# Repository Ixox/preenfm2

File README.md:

# preenfm2 firmware

Ixox/preenfm2 is the official repository of the preenfm2 firmware.

You can find here the compiled firmware, its code source and some hardware files for the PCB, MCU board and cases.

To flash the preenfm2 for the first time, [follow these instructions](https://github.com/Ixox/preenfm2/tree/master/flash)

## Compiling the firmware

To compile the firmware, you'll need [arm-gcc version 4.7](https://launchpad.net/gcc-arm-embedded/+milestone/4.7-2014-q2-update)

Add the bin directory to your PATH, and run **'make'**, you'll get the list of the available targets.

```bash
$ make
You must chose a target 
Don't forget to clean between different build targets
   clean : clean build directory
   pfm : build pfm2 firmware
   pfmcv : build pfm2 firmware for Eurorack 
   installdfu : flash last compiled firmware through DFU
   zip : create zip with all inside
```
Since some refactoring, the bootloader does not compile anymore. But it's available in its binary format.

Then put your preenfm2 in [bootloader mode](http://ixox.fr/preenfm2/manual/upgrade-firmware/). Look at DFU part 4.

To flash the firmware on the preenfm2 using the DFU protocol :

```bash
make installdfu
```

Once it's done, unplug the power cable and plug it back.

## New Filters in 2.11

Many effects have been added in the firmware 2.11. They were coded by [Toltekradiation](http://ixox.fr/forum/index.php?topic=69544.0).

His github repo is [here](https://github.com/pvig/preenfm2). You'll find there some description of the different effects.

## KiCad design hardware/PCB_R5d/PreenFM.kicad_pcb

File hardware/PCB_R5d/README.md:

# Preenfm2 PCB files

Here is the preenfm2 PCB files : revision r5d.<br />
Made with [Kicad](http://kicad-pcb.org/) 3.<br />

<br />
### What's new ?<br />
Compared to r5c, there is an additional resistor that makes [the yellow oled mod](http://ixox.fr/forum/index.php?topic=69159.0) much easier.<br />

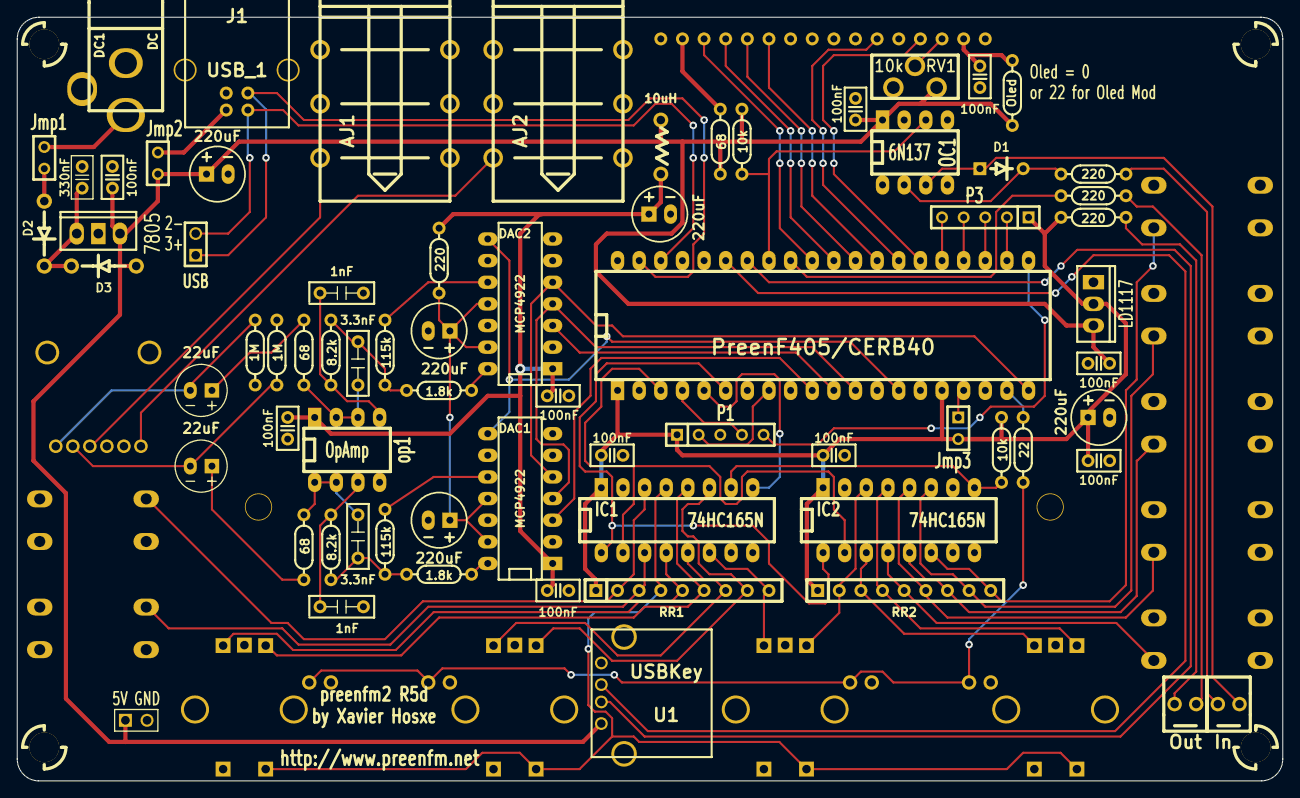
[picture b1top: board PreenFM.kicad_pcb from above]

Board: 2 copper layers, 148.6 x 89.7 mm, 92 parts (0 on the bottom side), 80 nets.

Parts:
3V1: LD1117; FMLD1117
5V1: 7805; FM7805
AJ1, AJ2: AUDIO_JACK; FMJACK
C1, C2, C3, C5, C7, C8, C10, C14, C19, C23: 100nF; FMCondeDecouplage2
C4: PreenF405/CERB40; DIP-40__600_ELL
C6, C9, C11, C13, C22: 220uF; FMCondoChimique2
C12: 330nF; FMCondeDecouplage
C15, C16: 1nF; FMCondoPlastic
C17, C18: 3.3nF; FMCondoPlastic
C20, C21: 22uF; FMCondoChimique_10uF_2
D1: 1N4148; FMDiode2
D2, D3: 1N4001; FMDiode1N4001_2
DAC1, DAC2: MCP4922; FM_mcp4922_2
DC1: DC; JACK_ALIM4
Enc1, Enc2, Enc3, Enc4: ENCODER_SW; FMEncoderWithSwitch2
IC1, IC2: 74HC165N; DIP-16__300_ELL
J1: USB_1; FMUSB2
Jmp1, Jmp2, Jmp3: Jmp; SIL-2
K2: USB; SIL-2
L1: 10uH; FMInductance
L2, L3, L4, L5: LED; FMLed
LCD1: Disp_20x4; FMLCD4x20_2
M1: In; FMMidi2
M2: Out; FMMidi2
OC1: 6N137; DIP-8__300_ELL
P1, P3: CONN_5; SIL-5
P4, P5, P6, P7: CONN_1; FMHole3mm
POW1: 5V; PIN_ARRAY_2X1
R1, R2, R3, R6: 220; FMResistance
R4, R5: 10k; FMResistance
R7, R9: 1.8k; FMResistance
R8, R10: 115k; FMResistance
R11, R14, R15: 68; FMResistance
R12, R13: 8.2k; FMResistance
R16, R17: 1M; FMResistance
R18: 22; FMResistance
R19: Oled; FMResistance
RR1, RR2: RR10k; FMRR9
RV1: 10k; FMRV2
S1, S2, S3, S4, S5, S6, S7: SWITCH; FMButton2
U1: USBKey; FMUSB_A
V1: VOLUME; FMDualPotALPS
op1: OpAmp; DIP-8__300_ELL

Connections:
+3.3V: 3V1.2, C1.1, C2.1, C4.1, C4.16, C9.1, C23.1, IC1.16, IC2.16, Jmp3.2, P1.1, P3.1, R1.2, R4.1, RR1.1, RR2.1
+5V: C6.1, C7.1, C8.1, C19.1, DAC1.1, DAC2.1, L1.2, R6.1, op1.8
+5VA: 3V1.3, 5V1.2, C3.1, C5.1, C10.1, C22.1, D3.1, Jmp2.1, L1.1, OC1.8, POW1.1, R5.2, R11.2, R19.2, RV1.3, U1.1
/AIN1: C4.22, P3.2
/AIN2: C4.23, P3.3
/AIN3: C4.24, P3.4
/AIN4: C4.25, P3.5
/DB4: C4.28, LCD1.11
/DB5: C4.29, LCD1.12
/DB6: C4.30, LCD1.13
/DB7: C4.31, LCD1.14
/E: C4.27, LCD1.6
/LED: C4.19, R18.1
/LODR: C4.17, Jmp3.1
/MCLK: C4.3, IC1.2, IC2.2
/MLD: C4.6, IC1.1, IC2.1
/MQH: C4.5, IC1.9
/RESET: C4.21, P1.5
/RR1_1: IC1.14, RR1.2, S2.2
/RR1_2: IC1.3, RR1.3, S1.2
/RR1_3: Enc1.3, Enc2.3, Enc3.3, Enc4.3, IC1.13, RR1.4
/RR1_4: Enc4.2, IC1.4, RR1.5
/RR1_5: Enc4.0, IC1.12, RR1.6
/RR1_6: Enc3.2, IC1.5, RR1.7
/RR1_7: Enc3.0, IC1.11, RR1.8
/RR1_8: Enc2.2, IC1.6, RR1.9
/RR2_1: Enc2.0, IC2.14, RR2.2
/RR2_2: Enc1.2, IC2.3, RR2.3
/RR2_3: Enc1.0, IC2.13, RR2.4
/RR2_4: IC2.4, RR2.5, S3.2
/RR2_5: IC2.12, RR2.6, S4.2
/RR2_6: IC2.5, RR2.7, S5.2
/RR2_7: IC2.11, RR2.8, S6.2
/RR2_8: IC2.6, RR2.9, S7.2
/RS: C4.26, LCD1.4
/RX: C4.33, OC1.6, R5.1
/SPI_CK: C4.12, DAC1.4, DAC2.4
/SPI_DAC1: C4.10, DAC1.3
/SPI_DAC2: C4.11, DAC2.3
/SPI_LDAC: C4.14, DAC1.8, DAC2.8
/SPI_MO: C4.20, DAC1.5, DAC2.5
/SWD_CLK: C4.8, P1.2
/SWD_IO: C4.4, P1.4
/TX: C4.32, R3.2
/USB_D+: C4.39, J1.3, K2.1
/USB_D-: C4.38, J1.2, K2.2
/USB_DN: C4.34, U1.2
/USB_DP: C4.35, U1.3
GND: 3V1.1, 5V1.1, AJ1.0, AJ2.0, C1.2, C2.2, C3.2, C4.2, C5.2, C6.2, C7.2, C8.2, C9.2, C10.2, C11.2, C12.2, C13.2, C14.2, C15.2, C16.2, C19.2, C22.2, C23.2, DAC1.12, DAC2.12, DC1.1, Enc1.1, Enc1.4, Enc2.1, Enc2.4, Enc3.1, Enc3.4, Enc4.1, Enc4.4, IC1.8, IC1.15, IC2.8, IC2.15, J1.4, L2.2, L3.2, L4.2, L5.2, LCD1.1, LCD1.5, LCD1.7, LCD1.8, LCD1.9, LCD1.10, LCD1.16, OC1.5, P1.3, POW1.2, R16.2, R17.2, RV1.1, S1.1, S2.1, S3.1, S4.1, S5.1, S6.1, S7.1, U1.4, V1.1, V1.4, op1.4
unnamed: IC1.10, IC2.9, R4.2
unnamed: AJ1.1, V1.5
unnamed: M2.1, R1.1
unnamed: C17.1, R14.1, op1.1, op1.2
unnamed: C18.1, R15.1, op1.6, op1.7
unnamed: C20.1, R14.2
unnamed: C21.1, R15.2
unnamed: DAC1.14, R7.1
unnamed: C15.1, R13.2, op1.5
unnamed: DAC2.14, R9.1
unnamed: DAC2.10, R10.1
unnamed: DAC1.10, R8.1
unnamed: C17.2, R7.2, R8.2, R12.1
unnamed: AJ2.1, V1.2
unnamed: C20.2, R16.1, V1.6
unnamed: D2.1, Jmp1.2
unnamed: DC1.3, Jmp1.1
unnamed: LCD1.15, R11.1
unnamed: C16.1, R12.2, op1.3
unnamed: J1.1, Jmp2.2
unnamed: LCD1.3, RV1.2
unnamed: M1.1, R2.1
unnamed: M2.2, R3.1
unnamed: D1.2, OC1.2, R2.2
unnamed: D1.1, M1.2, OC1.3
unnamed: C18.2, R9.2, R10.2, R13.1
unnamed: 5V1.3, C12.1, D2.2, D3.2
unnamed: C21.2, R17.1, V1.3
unnamed: C14.1, LCD1.2, R19.1
unnamed: C11.1, C13.1, DAC1.11, DAC1.13, DAC2.11, DAC2.13, R6.2
unnamed: L2.1, L3.1, L4.1, L5.1, R18.2

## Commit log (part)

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2014-01-16 Fixed velocity in ALGO17 & 18
2014-01-18 First FX commit : LP, HP, Bass, Mono.
2014-01-18 FX default value cannot be (0,0,0,0)
2014-01-26 1.B2 : fix + new mixer + CC as source + OLED screen saver + New LFO
2014-02-01 Better navigation with double press in Matrix menu
2014-02-04 1.B4 Better DX7 import
2014-02-06 New hardfault page
2014-02-06 Fixed voice allocation bugs. getFreeVoice + Timbre::preenNewNote.
2014-03-05 1.B6 : fixed glide display bug + USB aftertouch Iternal refactoring
2014-03-11 Add direction 'played' to arpeggiator
2014-03-12 1.B7 : Fixed channe 3&4 but
2014-03-13 1.B8 : arpeggiator as played + note on alocation reworked
2014-03-15 Silence warnings...
2014-03-15 Less verbose makefile
2014-03-16 Bootloader 1.11
2014-03-16 Better push timer for bootloader
2014-03-20 1.B9... Makefile & TODO updated
2014-03-20 ALGO28 : only show IM1
2014-03-22 1.B9: Bank, BankLSB and program change implemented.
2014-03-23 Removed ugly Display debug
2014-03-23 Correct version : 1.B10
2014-03-26 1.B11 : LFO.Ksyn => 16.0s + several small fixes in the LF area
2014-03-28 Experimental user-defined pattern for arpeggiator
2014-03-28 Rename engineApr to engineArp (probably just a typo)
2014-03-28 Store user arp pattern (contents might still change though)
2014-03-29 Store arpeggiator patterns in a uint32_t instead of 4 floats, allowing for 4 per timbre. Add specific editing code (rough implementation)
2014-04-02 Performance patch: mostly from Patrick perf Dowling branch.
2014-04-03 Makefile 1.B12 + KSyn display fixe bug (4.00 correctly displayed)
2014-04-09 Ensure valid menu row when switching instruments, return to last state
2014-04-10 Fix boundary case of navigation, move #define to header
2014-04-10 Change compile-time edit option a run-time configurable setting; rename to 'unlinked' editing so false default works
2014-04-11 Fix typo in matrix target (Mix3/pan3)
2014-04-12 Fix regression in navigation and use correct button for env rows
2014-04-12 Add comment
2014-04-27 Add cyclic modes for arpeggiator
2014-04-29 Minor cleanup, rename arp modes
2014-05-02 Remove unused virtual function calls, save some cycles...
2014-05-02 Remove useless code + move code to cpp
2014-05-03 Patrick bug fix
2014-05-07 Midi CC fix
2014-05-16 Firmware 1.00 ready ?
2014-06-05 Fix combo problem + firmware 1.01
2014-06-17 StepSequers & preset name flushed with presets
2014-06-29 Better name refresh
2014-07-15 Swap to page shortcuts
2014-07-15 1.03 : nrpn preset flush are now done correctly on the right midi channel
2014-08-10 Small insignifiant details
2014-09-08 Randomizer + boot sound
2014-09-08 BP middle freq is targetable from the Matrix
2014-10-12 Fix LFO with ksyn = 0.01
2015-08-09 1.07b1 Scala
2015-08-11 compilation error on Linux fixed.
2015-08-11 Lfo phases + Midi note scaling
2015-08-17 Real polyphony
2015-08-18 Fix Modwheel, Pitchbend bug
2015-08-19 1.99c : 2 midi note scales + Gate back
2015-08-20 1.99c : matrix target list updated
2015-08-27 1.99d save
2015-08-28 2.00b1 see TODO.txt
2015-08-28 2.00b1 last minute change :(
2015-10-05 First version of user waveforms
2015-10-10 All waveforms between -1.0 and 1.0
2015-10-15 2.02 : user waveform preprocessing
2016-05-08 2.03 : more CC
2016-08-24 2.05B3
2016-09-14 Breath CC to matrix source
2016-09-14 FIX : IM* target matrix can correctly decrease velocity IM
2016-09-19 Strict NRPN option added : use 7bits (CC6 only) when sufficient
2016-09-24 PreenF405 README
2016-10-11 Revert "Strict NRPN option added : use 7bits (CC6 only) when sufficient"
    This reverts commit 4ffa40c3e819c186cf1b49844e744488c2d04e78.
2016-10-12 New midi CC for arpegiator
2016-10-12 Fix missing note... Stupid return instead of continue :/
2016-10-12 2.06
2016-11-16 New svg case files
2016-11-17 hardwae/case : hardware list added
2016-11-17 Create gh-pages branch via GitHub
2016-12-16 Fix MTX* problem
2017-05-29 PCB r5d files added
2017-05-29 Better README.md
2017-07-12 Add preenF405 detailed BOM
2017-10-15 Copy feature
2017-10-16 Lokki's feature : global midi channel + hertz osc detune
2017-10-22 2.08b2 lfo rate up to 99.9hz +fixes
2017-10-23 2.08b3 : add CC for env modulators and carriers
2017-10-23 release/fw_2.08b3 firmware
2017-10-24 Matrix destination can control Carrier vs Modulatir Env*
2017-10-24 Firmware 2.08b4
2017-11-05 Fix NRPN step sequencer
2017-11-05 2.08 binary added
2017-11-05 2.08 REAMDE.md
2017-11-05 2.08 README.md changes
2017-11-07 CC cannot make filter Freq and Res > 1.00
2018-04-02 2.08b env bug fix
2018-10-13 Scala Enabled and Scale controlable through midi CC
2018-10-13 Fix Op 1&4 default combo release time
2018-10-13 2.08c was already used
2018-10-14 Reset internal cached values between notes
2018-10-27 Prevent reading null pointer when receiving midi value > max
2018-10-27 Move ARP CC to 100+ to prevent confustion with NRPN
2018-10-27 Update correctly * (preset modified) for instruments not on screen
2018-10-27 Display refresh optimisation on midi update + fix some preset display that show up when it should not
2018-12-31 Update to latest 4.7 gcc release.
2019-03-08 Van Daal Electronics CB converter PCB added
2019-03-08 Update URL
2019-04-03 Welcome Emilie in the preenfm2 code
2019-05-04 Schematics in pdf
2019-05-30 New combo bank now shows up correctly
2019-05-30 New midi channel for current instrument + new CC(119) to modify current instrument
2019-05-30 New case svg files added
2019-05-30 Analog in of P3 enabled
2019-05-30 Fix bug with Gate On when switch on
2019-05-30 Eurorack + gate + v/oct + tunable
2019-05-30 Fix Makefile
2019-05-30 Put back modifiable CV gate
2019-05-30 CVGate can trigger several instruments
2019-08-08 new filter flavour + tilt filter
2019-08-08 added lost commit
2019-08-09 tilt fix
2019-08-10 some filter tweak+code cleaning
2019-08-10 added allpass, saturator & sigmoid filters
2019-08-11 sigmoid tweak
2019-08-11 more usable range for saturator
2019-08-11 allpass filter used for a stereo enhancer filter
2019-08-13 dist & sigmoid tweak
2019-08-14 added xor & foldback distortion
2019-08-15 fixed sigmoid level + changed fold algo
2019-08-15 missing matrix filter controls added
2019-08-15 lowered resonance in tilt filter
2019-08-16 lp2 & hp2 reso saturation fix
2019-08-17 various optimizations & waveshaping here and here
2019-08-17 wrap filter added
2019-08-18 added swap~ fx + threshol voicenum attenuation
2019-08-18 fx threshold tweak
2019-08-21 hp2 bug fix + texture fx try + some tweak
2019-08-22 changed fx swap and texture to texture1 & 2 = bitmangling fx
2019-08-22 allow texture1&2 to be matrix controlled
2019-08-25 added lphp filter
2019-08-26 added BP3 + sorted fx list by use (more or less)
2019-08-26 edited readme + LPws
2019-08-26 readme update
2019-08-27 added notch & lp3 filters
2019-08-28 added PEAK, HP3, BP3 + renamed old BP3 -> BPds
2019-08-29 added bell filter
2019-08-29 various tweak + readme update
2019-08-30 wrap & fold rework + code cleaning
2019-08-30 added tone to distortion fx + tweak
2019-08-30 optimisation
2019-08-31 lp2&hp2 offset
2019-08-31 svf volume compensation
2019-09-01 code cleaning
2019-09-01 lphp & BPds resonance tweak
2019-09-02 added lowshelf & highshelf filters
2019-09-04 drastic optimizations
2019-09-05 float cast optimization
2019-09-06 sat33, sigmoid, lp resonance tweak
2019-09-10 sig, fold, wrap filter change
2019-09-11 sigm, fold, wrap
2019-09-13 FILTER_LPXOR rework
2019-09-21 svf filters cleanup, added LPSin, HPSin, BPSin
2019-09-25 lpsin now use svf lp
2019-09-27 satSin fix + optimization
2019-09-29 added doublenotch + optimization
2019-10-04 reworked pann, ap3
2019-10-05 resonant 3xap, tilt ap, sat ap, 3xnoth ap3 pan
2019-10-05 texture1&2 : added ap diffusion
2019-10-06 textures slight mod + rollback some ap filters
2019-10-10 AP4D : Diffusion allpass filter + ap fx tweak
2019-10-12 ap on svf + various tweak
2019-10-18 allpass allpass
2019-10-23 formantic filter + ap polish
2019-10-26 formant filter wip
2019-10-27 formant + ap4 fine tune
2019-11-01 tanh optimization, formant filter tweak
2019-11-05 added ladder filter
2019-11-19 wip oryx2, ladders..
2019-11-21 oryx + ladders wip
2019-11-24 formant wip
2019-11-25 formants fine tune
2019-11-30 added h3o+ filter
2019-12-01 h3o+ wip
2019-12-05 various tweak
2019-12-07 srr + tb wip
2019-12-08 tb2 + crush2 wip
2019-12-09 code cleaning + tbcrunchtweak
2019-12-10 crush wip
2019-12-11 reworked srrx2 & Svh3
2019-12-12 Alkx fine tuning
2019-12-14 Put back original README + filters part added
2019-12-14 Fix possible problem when number of voice is increased
2019-12-14 fix to allow adcIn merge
2019-12-14 velocity fix + code cleaning
2019-12-14 h3o+ : remove accent circuit
2019-12-14 accent is back on teebee filter
2019-12-15 bpds self oscillation fix
2019-12-15 18db resonance tweak
2019-12-15 peak reso curve tweak
2020-01-09 added 8 matrix sources
2020-01-09 matrixSourcePosition for CVIN fix
2020-01-11 README : makefile target list updated
2020-01-11 Add bootloader bin in zip file
2020-01-14 renamed source + oryx rollbck
2020-01-17 why not [more matrix sources] ?
2020-01-20 oryx3 rework + sources
2020-01-26 texture2 rework &+
2020-02-04 textures wip + sin f control
2020-02-05 fine tune levels
2020-02-08 filter controls wip
2020-02-09 lp3, rot
2020-02-19 + glide gate
2020-02-21 rot fix
2020-02-28 glide wip
2020-03-08 better glide
2020-03-16 articulation121
2020-03-20 glide skew...
2020-03-25 hold pb fix
2020-03-26 code cleanup
2020-03-27 end existing gliding in all cases
2020-03-28 stop voice assignation bouncing
2020-03-29 +2 more glide vals
2020-04-04 glide mods fix &+
2020-04-05 2.11 : new instrunet selection for Eurorack version
2020-04-06 mono glide over poly + cleaning
2020-04-06 polyglide branch
2020-04-15 added editor xml definitions
2020-04-30 modulator env loop
2020-05-01 added sustain in env loop
2020-05-07 bug fix & optimisation
2020-05-08 matrix seq start bug fix
2020-05-21 Destination 2 added
2020-05-21 Features from Patrice Vigouroux
2020-05-22 Dedicated #define for CPU_USAGE
2020-05-22 Fix typ
2020-05-22 Fix Dest2 lfoused for MX1/MX4
2020-05-22 Beta1 ready
2020-05-24 updates from 2.12
2020-05-27 more consistent step start result
2020-05-27 updated version
2020-05-29 stepseq fix for ENV_ATTACK destinations
2020-06-28 Not working yet
2020-06-28 Compiles
2020-07-03 CC10 & CC7 & 3 bug fixes
2020-07-03 Remove BOOTLOADER define
2020-07-04 IRQ/DMA ready to test
2020-07-04 2.12 bug fix
2020-07-05 removed GLIDE_ for lighter cpu charge
2020-07-07 Next step
2020-07-09 CS4344 fix IRQ and Frequencies
2020-07-11 matrix dest label fix
2020-07-12 Bootloader read UsbKey and DFU OK
2020-07-14 USB optimization
2020-07-22 Optimization GPIO / LCD / USART
2020-08-15 CS4344 fixes
2020-08-16 Samples are uint32 / CS4344 real 24 bits / Wait with message if no USB Key
2020-08-18 Flash README
2020-08-21 Message when no Usb Key instead of freezing
2020-08-21 CC10 & CC7 / 3 bug fixed / 192Mhz is the new default
2020-08-21 Mix4/Pan4 destination fixed / small optimization
2020-08-21 CS4344
2020-09-19 Better midi and screen boot
2020-09-20 bootlader 1.12 OK
2020-10-03 stutil debug json files
2020-10-16 Upgrade to FatFs 0.14
2020-10-25 Leave more time to USB stick to init before displaying message
2020-10-25 Fix first bit problem with i2s (sound saturation)
2020-10-25 Bootloader 1.13 (not finished)
2020-10-25 Fix screensaver
2020-10-27 Bootloader modificaiton (USB access still does not work)
2020-10-28 Bootloader 1.13 with USB access working
2020-11-06 flash/README updated
2020-11-06 flash README.md updated
2020-11-06 3D printed case added
2020-11-06 update case3DPrint/README
2021-02-15 Unisons seems to work
2021-02-16 Bug fix : load preset freeze + button shortcut
2021-02-16 Fix bug : UI + presets
2021-02-21 Unisons : CV fixed + different starting phase per voice
2021-02-22 Correct initialization of unison phases
2021-02-22 Better unison phases + stop unison when changing number of voices
2021-03-06 Add midi CC (13,14) for unison spread and detune
2021-03-20 2.21 + stop sound when changing play mode (poly/unison)
2021-03-28 Top Surface PCB v1.0
2021-04-13 Fix non-pfm2 sysex problem
2021-04-13 Update debug name
2021-04-17 Case_PCB readme added
2021-04-17 CASE_PCB added picture
2021-08-22 2.21b : Fix Attk midi CC
2024-01-19 vosim like
2024-01-20 algo display + mod range
2024-01-20 lfo noise shape
